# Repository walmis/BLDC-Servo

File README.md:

# BLDC-Servo

This project implements a FOC motor controller board for 57BLF0x series NEMA brushless motor.

The project goals are:
* to be inexpensive
* fully support FOC drive
* smooth operation for FFB devices
* Large stalled torque == relatively large current drive

The main components are:
* STM32L412 or STM32F103C8T6 MCU
* NCP81151 - MOSFET Gate drivers
* NCS213/INA213 current sense amplifiers
* FDMS8018 N-channel MOSFETS (can be any TDSON-8 30V>= MOSFETS with required current rating)
* MP2359 DC-DC step-down
* SN75176B RS485 transceiver

The board attaches directly to the motor casing with mosfets in direct contact (with thermal paste). This makes a good heatsink for power dissipation.

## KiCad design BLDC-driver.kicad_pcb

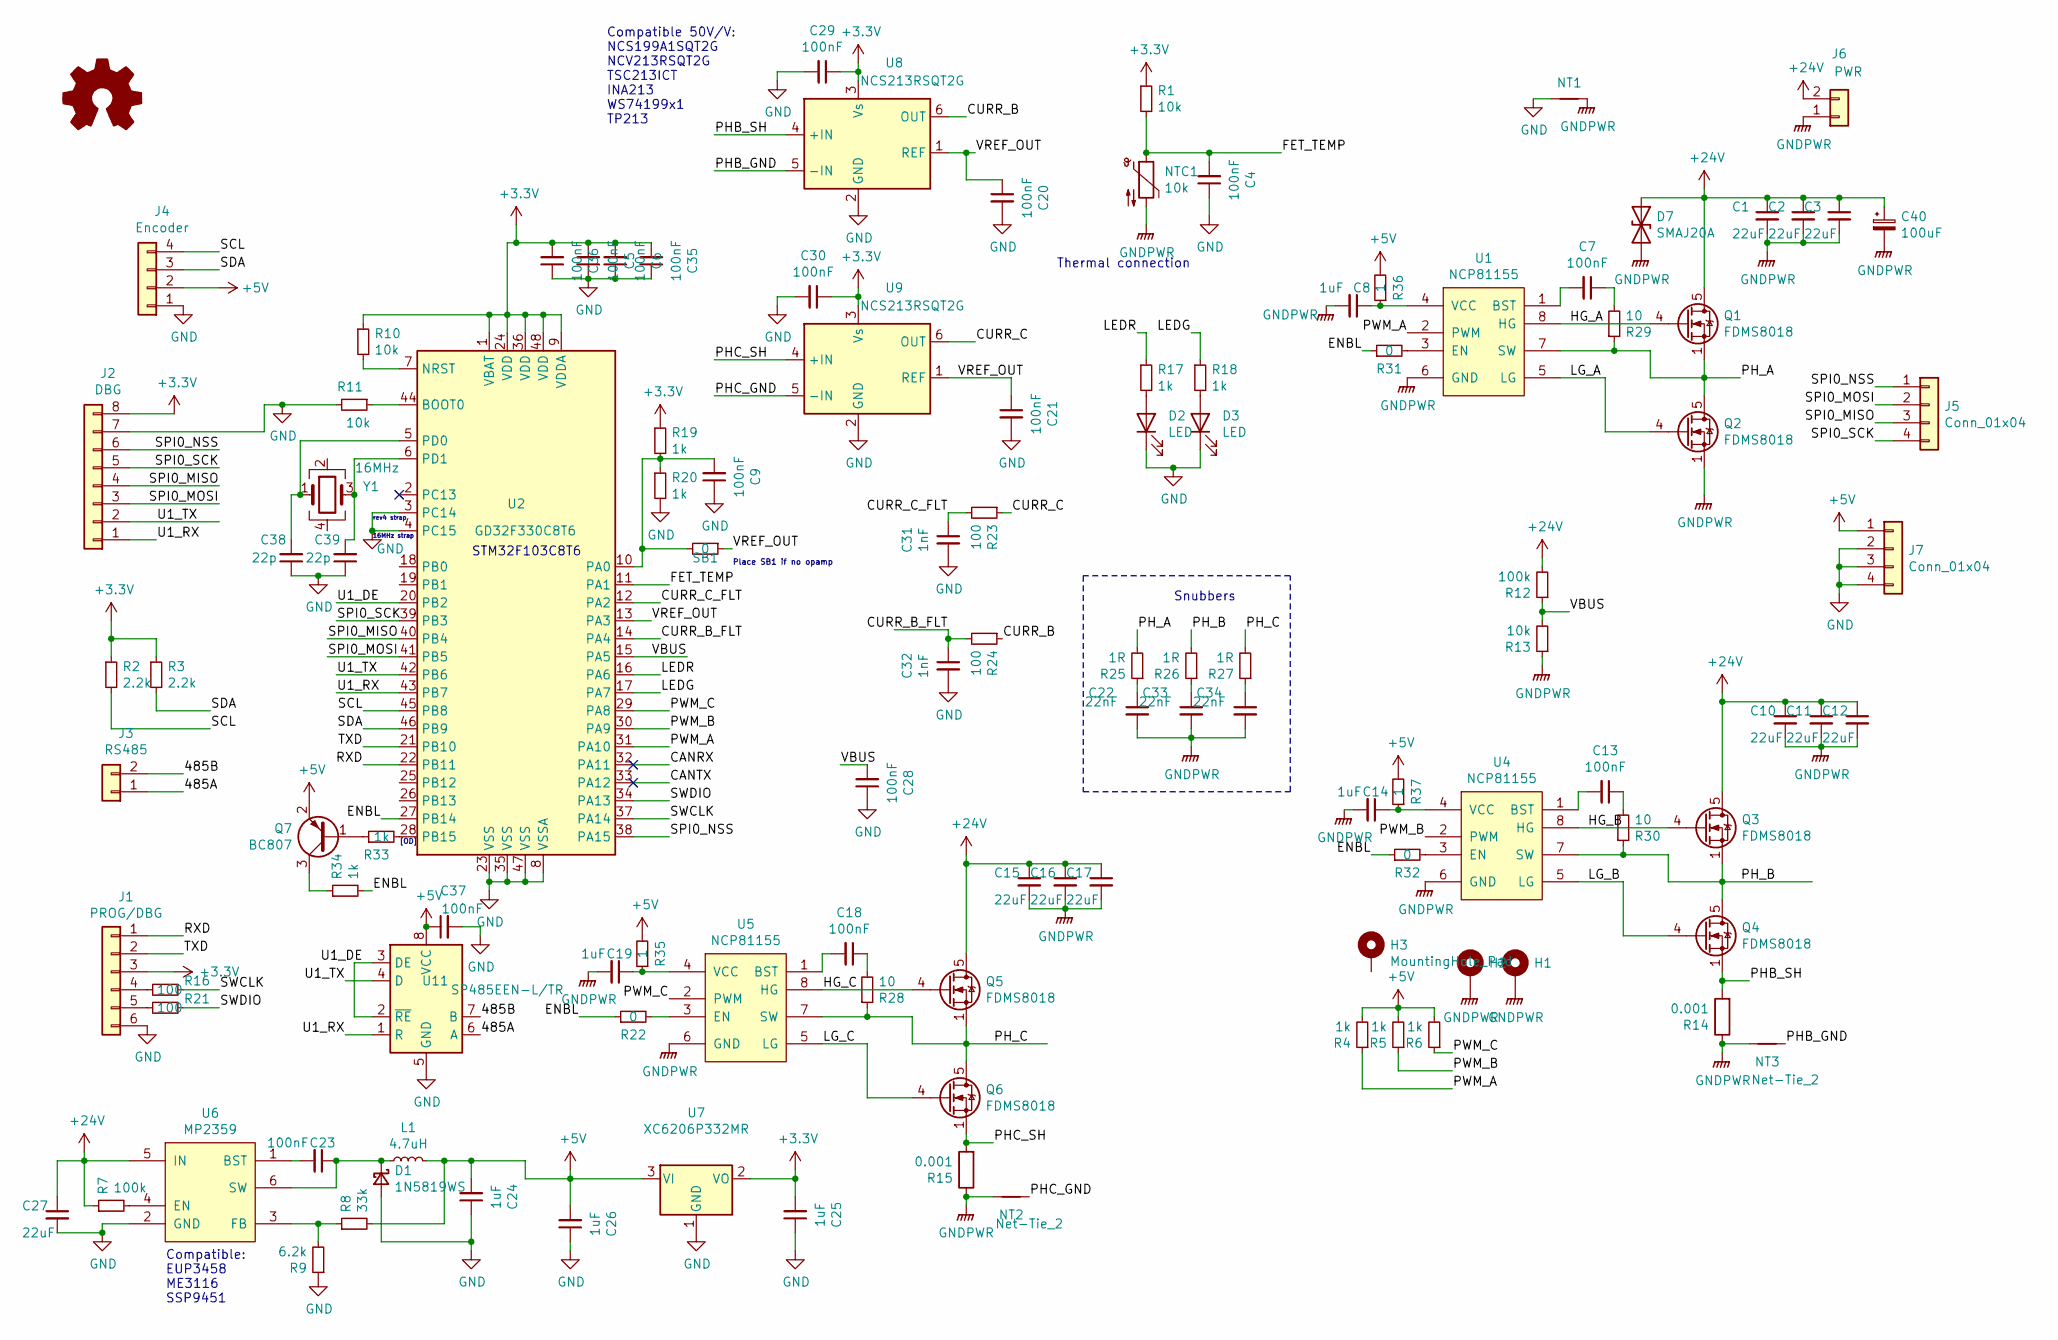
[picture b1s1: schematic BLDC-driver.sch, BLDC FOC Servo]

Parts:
C1, C2, C3, C10, C11, C12, C15, C16, C17, C27: 22uF; C_1206_3216Metric; MPN CL31A226KAHNNNE; JLCSMT C12891
C4, C5, C6, C7, C9, C13, C18, C20, C21, C23, C28, C29, C30, C35, C36, C37: 100nF; C_0402_1005Metric; MPN CL05B104KO5NNNC; JLCSMT C1525
C8, C14, C19, C24: 1uF; C_0402_1005Metric; MPN CL05A105KA5NQNC; JLCSMT C52923
C22, C33, C34: 22nF; C_0402_1005Metric; MPN 0402B223K500NT; JLCSMT C1532
C25, C26: 1uF; C_0603_1608Metric; MPN CL10A105KB8NNNC; JLCSMT C15849
C31, C32: 1nF; C_0402_1005Metric; MPN 0402B102K500NT; JLCSMT C1523
C38, C39: 22p; C_0402_1005Metric; MPN 0402CG220J500NT; JLCSMT C1555
C40: 100uF; CP_Elec_8x6.5; MPN UT1E101M0806VG; JLCSMT C393805
D1: 1N5819WS; D_SOD-323; MPN 1N5819WS; JLCSMT C191023
D2, D3: LED; LED_0603_1608Metric; MPN 19-217/GHC-YR1S2/3T; JLCSMT C72043
D7: SMAJ20A; D_SMB; MPN SMAJ20CA; JLCSMT C309871
H1, H2, H3: MountingHole_Pad; MountingHole_3.2mm_M3_DIN965_Pad_TopOnly; JLCPCB_IGNORE 1
J1: PROG/DBG; JST_PH_S6B-PH-K_1x06_P2.00mm_Horizontal; JLCPCB_IGNORE 1
J2: DBG; PinHeader_1x08_P2.00mm_Vertical; JLCPCB_IGNORE 1
J3: RS485; JST_PH_S2B-PH-K_1x02_P2.00mm_Horizontal; JLCPCB_IGNORE 1
J4: Encoder; PinSocket_1x04_P2.00mm_Vertical; JLCPCB_IGNORE 1
J5, J7: Conn_01x04; PinHeader_1x04_P2.00mm_Vertical; JLCPCB_IGNORE 1
J6: PWR; JST_VH_B2PS-VH_1x02_P3.96mm_Horizontal; JLCPCB_IGNORE 1
L1: 4.7uH; L_Taiyo-Yuden_MD-3030; MPN WPN3012HS4R7MT; JLCSMT C305275
NT1, NT2, NT3: Net-Tie_2; NetTie-2_SMD_Pad0.5mm; JLCPCB_IGNORE 1
NTC1: 10k; R_0603_1608Metric; MPN NCP18XH103F03RB; JLCSMT C13564
Q1, Q2, Q3, Q4, Q5, Q6: FDMS8018; JLCPCB_IGNORE 1
Q7: BC807; SOT-23; MPN MMBT5401; JLCSMT C8326
R1, R10, R11, R13: 10k; R_0402_1005Metric; MPN 0402WGF1002TCE; JLCSMT C25744
R2, R3: 2.2k; R_0603_1608Metric; MPN 0603WAF2201T5E; JLCSMT_PKG 0603
R4, R5, R6, R19, R20, R33, R34: 1k; R_0402_1005Metric; MPN 0402WGF1001TCE; JLCSMT_PKG 0402
R7, R12: 100k; R_0402_1005Metric; MPN 0402WGF1003TCE; JLCSMT C25741
R8: 33k; R_0603_1608Metric; MPN 0603WAF3302T5E; JLCSMT C4216
R9: 6.2k; R_0603_1608Metric; MPN 0603WAF6201T5E; JLCSMT_PKG 0603
R14, R15: 0.001; R_1210_3225Metric; MPN LR1206-21R001F4; JLCSMT C154629
R16, R21, R23, R24: 100; R_0402_1005Metric; MPN 0402WGF1000TCE; JLCSMT_PKG 0402
R17, R18: 1k; R_0603_1608Metric; MPN 0603WAF1001T5E; JLCSMT_PKG 0603
R22, R31, R32: 0; R_0603_1608Metric; MPN 0603WAF0000T5E; JLCSMT C21189
R25, R26, R27: 1R; R_0402_1005Metric; MPN 0402WGF100KTCE; JLCSMT_PKG 0402
R28, R29, R30: 10; R_0402_1005Metric; MPN 0402WGF100JTCE; JLCSMT_PKG 0402
R35, R36, R37: 1; R_0402_1005Metric; MPN 0402WGF100KTCE; JLCSMT C25086
SB1: 0; R_0402_1005Metric; MPN 0402WGF0000TCE; JLCSMT C17168
U1, U4, U5: NCP81155; DFN-8-1EP_3x3mm_P0.5mm_EP1.66x2.38mm; MPN NCP81155MNTXG; JLCSMT C173765
U2: GD32F330C8T6; LQFP-48_7x7mm_P0.5mm; MPN GD32F330C8T6; JLCSMT C129291
U6: MP2359; SOT-23-6; MPN MP2359DJ-LF-Z; JLCSMT C14259
U7: XC6206P332MR; SOT-23; MPN XC6206P332MR; JLCSMT C5446
U8, U9: NCS213RSQT2G; SOT-363_SC-70-6; MPN INA199A1DCKR; JLCSMT C59135
U11: SP485EEN-L/TR; SOIC-8_3.9x4.9mm_P1.27mm; MPN SP485EEN-L/TR; JLCSMT C6855
Y1: 16MHz; Crystal_SMD_3225-4Pin_3.2x2.5mm; MPN X322516MLB4SI; JLCSMT C13738

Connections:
+3V3: C5.2, C6.2, C25.2, C29.1, C30.1, C35.2, C36.2, J1.3, J2.8, R1.1, R2.1, R3.1, R10.1, R19.1, U2.1 (VBAT), U2.9 (VDDA), U2.24 (VDD), U2.36 (VDD), U2.48 (VDD), U7.2 (VO), U8.3 (Vs), U9.3 (Vs)
+5V: C24.2, C26.2, C37.1, J4.2, J7.1, L1.2, Q7.2 (E), R4.2, R5.2, R6.2, R8.2, R35.2, R36.2, R37.2, U7.3 (VI), U11.8 (VCC)
+24V: C1.1, C2.1, C3.1, C10.1, C11.1, C12.1, C15.1, C16.1, C17.1, C27.1, C40.1, D7.1 (A1), J6.2, Q1.5 (D), Q3.5 (D), Q5.5 (D), R7.1, R12.2, U6.5 (IN)
/485A: J3.1, U11.6 (A)
/485B: J3.2, U11.7 (B)
/CANRX: U2.32 (PA11)
/CANTX: U2.33 (PA12)
/CURR_B: R24.1, U8.6 (OUT)
/CURR_B_FLT: C32.1, R24.2, U2.14 (PA4)
/CURR_C: R23.1, U9.6 (OUT)
/CURR_C_FLT: C31.1, R23.2, U2.12 (PA2)
/ENBL: R22.1, R31.1, R32.1, R34.2, U2.27 (PB14)
/FET_TEMP: C4.2, NTC1.1, R1.2, U2.11 (PA1)
/HG_A: Q1.4 (G), U1.8 (HG)
/HG_B: Q3.4 (G), U4.8 (HG)
/HG_C: Q5.4 (G), U5.8 (HG)
/LEDG: R18.1, U2.17 (PA7)
/LEDR: R17.1, U2.16 (PA6)
/LG_A: Q2.4 (G), U1.5 (LG)
/LG_B: Q4.4 (G), U4.5 (LG)
/LG_C: Q6.4 (G), U5.5 (LG)
/PHB_GND: NT3.2, U8.5 (-IN)
/PHB_SH: Q4.1 (S), Q4.2 (S), Q4.3 (S), R14.2, U8.4 (+IN)
/PHC_GND: NT2.2, U9.5 (-IN)
/PHC_SH: Q6.1 (S), Q6.2 (S), Q6.3 (S), R15.2, U9.4 (+IN)
/PH_A: Q1.1 (S), Q1.2 (S), Q1.3 (S), Q2.5 (D), R25.2, R29.1, U1.7 (SW)
/PH_B: Q3.1 (S), Q3.2 (S), Q3.3 (S), Q4.5 (D), R26.2, R30.1, U4.7 (SW)
/PH_C: Q5.1 (S), Q5.2 (S), Q5.3 (S), Q6.5 (D), R27.2, R28.1, U5.7 (SW)
/PWM_A: R4.1, U1.2 (PWM), U2.31 (PA10)
/PWM_B: R5.1, U2.30 (PA9), U4.2 (PWM)
/PWM_C: R6.1, U2.29 (PA8), U5.2 (PWM)
/RXD: J1.1, U2.22 (PB11)
/SCL: J4.4, R2.2, U2.45 (PB8)
/SDA: J4.3, R3.2, U2.46 (PB9)
/SPI0_MISO: J2.4, J5.3, U2.40 (PB4)
/SPI0_MOSI: J2.3, J5.2, U2.41 (PB5)
/SPI0_NSS: J2.6, J5.1, U2.38 (PA15)
/SPI0_SCK: J2.5, J5.4, U2.39 (PB3)
/SWCLK: R16.1, U2.37 (PA14)
/SWDIO: R21.1, U2.34 (PA13)
/TXD: J1.2, U2.21 (PB10)
/U1_DE: U2.20 (PB2), U11.2 (~RE), U11.3 (DE)
/U1_RX: J2.1, U2.43 (PB7), U11.1 (R)
/U1_TX: J2.2, U2.42 (PB6), U11.4 (D)
/VBUS: C28.2, R12.1, R13.2, U2.15 (PA5)
/VREF_OUT: C20.1, C21.1, SB1.1, U2.13 (PA3), U8.1 (REF), U9.1 (REF)
GND: C4.1, C5.1, C6.1, C9.1, C20.2, C21.2, C24.1, C25.1, C26.1, C27.2, C28.1, C29.2, C30.2, C31.2, C32.2, C35.1, C36.1, C37.2, C38.1, C39.1, D1.2 (A), D2.1 (K), D3.1 (K), J1.6, J2.7, J4.1, J7.2, J7.3, J7.4, NT1.1, R9.1, R11.2, R20.2, U2.3 (PC14), U2.4 (PC15), U2.8 (VSSA), U2.23 (VSS), U2.35 (VSS), U2.47 (VSS), U6.2 (GND), U7.1 (GND), U8.2 (GND), U9.2 (GND), U11.5 (GND)
GNDPWR: C1.2, C2.2, C3.2, C8.2, C10.2, C11.2, C12.2, C14.2, C15.2, C16.2, C17.2, C19.2, C22.2, C33.2, C34.2, C40.2, D7.2 (A2), H1.1, H2.1, J6.1, NT1.2, NT2.1, NT3.1, NTC1.2, Q2.1 (S), Q2.2 (S), Q2.3 (S), R13.1, R14.1, R15.1, U1.6 (GND), U1.9 (PAD), U4.6 (GND), U4.9 (PAD), U5.6 (GND), U5.9 (PAD)
unnamed: C7.1, R29.2
unnamed: C7.2, U1.1 (BST)
unnamed: C8.1, R36.1, U1.4 (VCC)
unnamed: C9.2, R19.2, R20.1, SB1.2, U2.10 (PA0)
unnamed: C13.1, R30.2
unnamed: C13.2, U4.1 (BST)
unnamed: C14.1, R37.1, U4.4 (VCC)
unnamed: C18.1, R28.2
unnamed: C18.2, U5.1 (BST)
unnamed: C19.1, R35.1, U5.4 (VCC)
unnamed: C22.1, R25.1
unnamed: C23.1, D1.1 (K), L1.1, U6.6 (SW)
unnamed: C23.2, U6.1 (BST)
unnamed: C33.1, R26.1
unnamed: C34.1, R27.1
unnamed: C38.2, U2.5 (PD0), Y1.1
unnamed: C39.2, U2.6 (PD1), Y1.3
unnamed: D2.2 (A), R17.2
unnamed: D3.2 (A), R18.2
unnamed: J1.4, R16.2
unnamed: J1.5, R21.2
unnamed: Q7.1 (B), R33.1
unnamed: Q7.3 (C), R34.1
unnamed: R7.2, U6.4 (EN)
unnamed: R8.1, R9.2, U6.3 (FB)
unnamed: R10.2, U2.7 (NRST)
unnamed: R11.1, U2.44 (BOOT0)
unnamed: R22.2, U5.3 (EN)
unnamed: R31.2, U1.3 (EN)
unnamed: R32.2, U4.3 (EN)
unnamed: R33.2, U2.28 (PB15)

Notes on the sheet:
Thermal connection
Snubbers
Place SB1 if no opamp
[OD]
Compatible 50V/V: NCS199A1SQT2G NCV213RSQT2G TSC213ICT INA213 WS74199x1 TP213
STM32F103C8T6
16MHz strap
Compatible: EUP3458 ME3116 SSP9451
rev4 strap

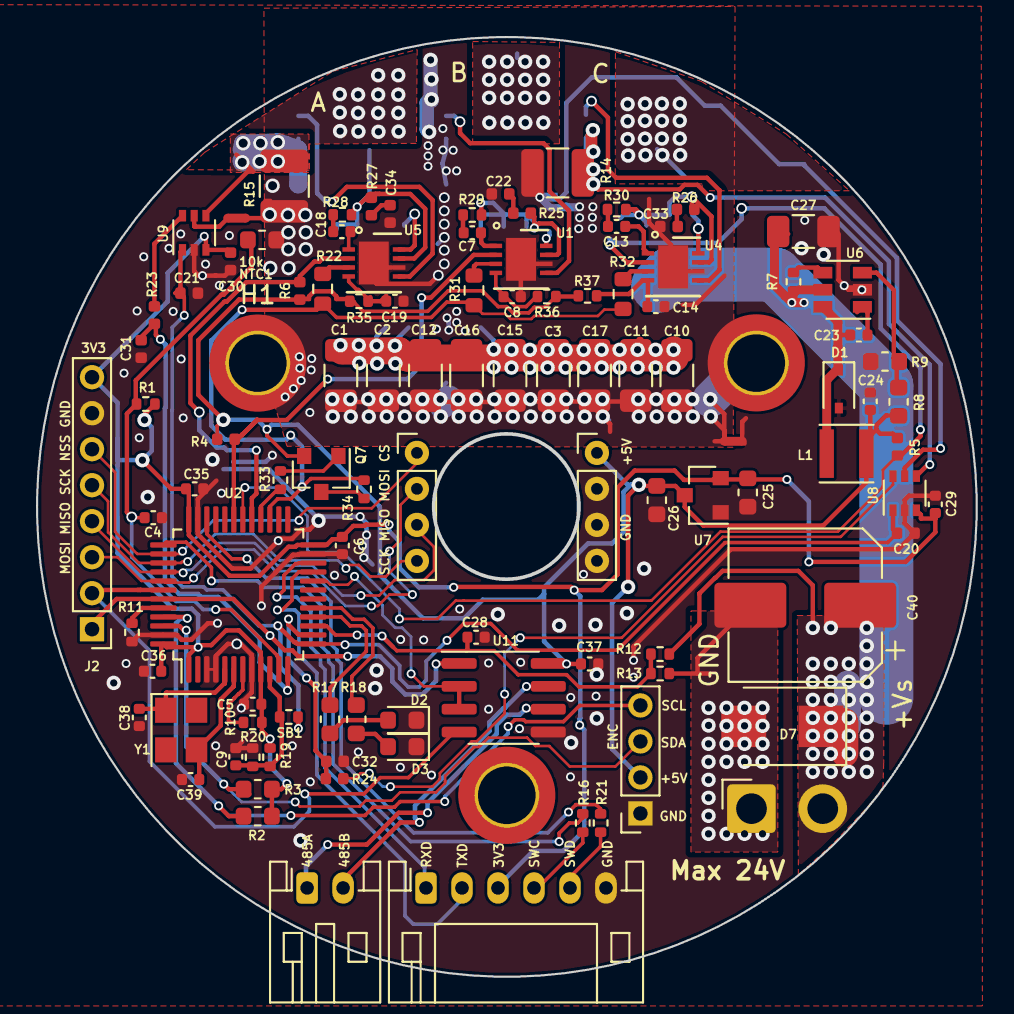
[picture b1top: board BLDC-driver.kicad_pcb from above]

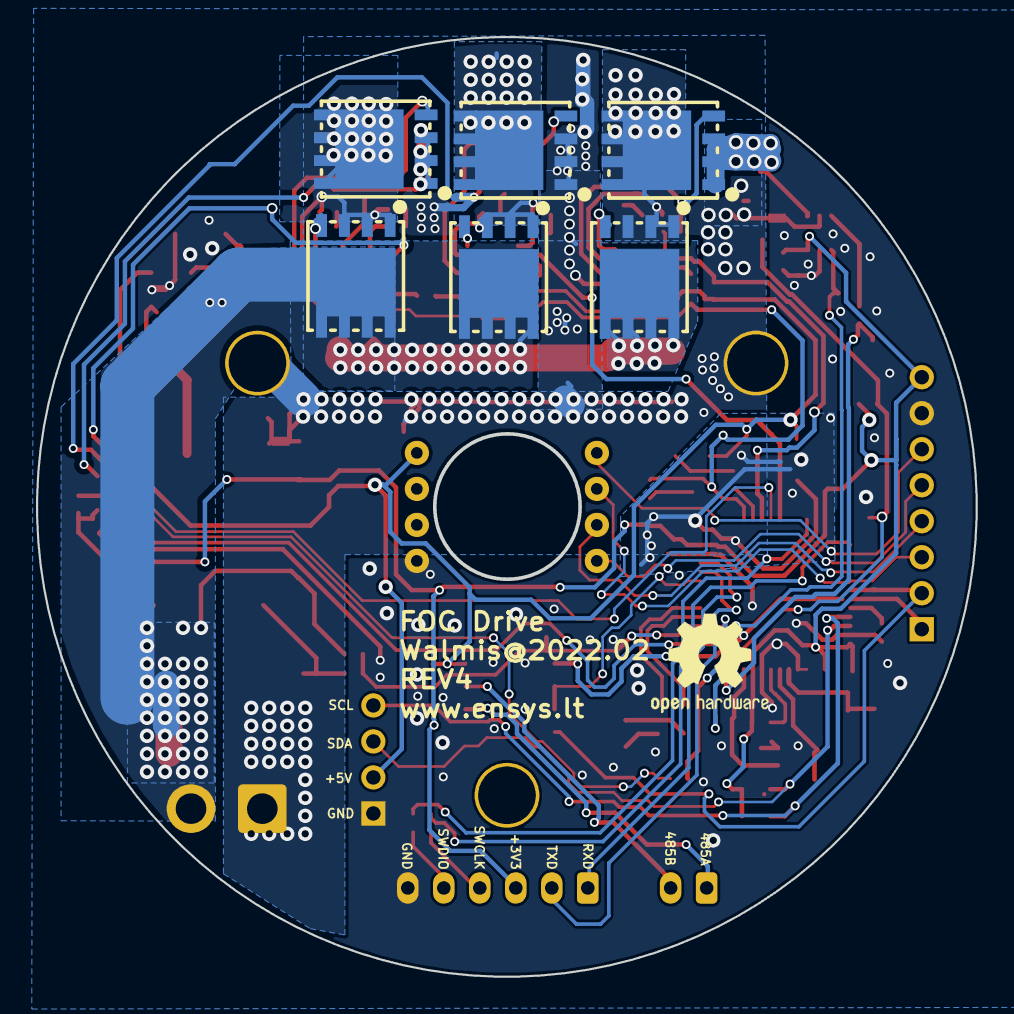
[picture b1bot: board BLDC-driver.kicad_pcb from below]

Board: 2 copper layers, 52.1 x 52.1 mm, 114 parts (7 on the bottom side), 77 nets.

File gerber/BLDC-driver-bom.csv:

"comment","designator","footprint","LCSC Part"
"100nF","C4,C5,C6,C7,C9,C13,C18,C20,C21,C23,C28,C29,C30,C35,C36,C37","0402","C1525"
"10uF","C1,C2,C3,C10,C11,C12,C15,C16,C17,C27","1206","C13585"
"1uF","C8,C14,C19,C24","0402","C52923"
"10k","NTC1","RES-SMD","C13564"
"10k","R1,R10,R11,R13","0402","C25744"
"1uF","C25,C26","0603","C15849"
"MP2359","U6","TSOT-23-6","C14259"
"6.2k","R9","0603","C4260"
"33k","R8","0603","C4216"
"4.7uH","L1","SMD,3x3x1.2mm","C305275"
"100k","R7,R12","0402","C25741"
"1k","R17,R18","0603","C21190"
"LED","D3","LED_0603","C72043"
"LED","D2","0603","C2286"
"0.001","R14,R15","RES-SMD","C154629"
"SMAJ24A","D7","SMA,DO-214AC","C10769"
"100","R16,R21,R23,R24","0402","C25076"
"1nF","C31,C32","0402","C1523"
"2.2k","R2,R3","0603","C4190"
"1k","R4,R5,R6,R19,R20,R33,R34","0402","C11702"
"1R","R25,R26,R27,R35,R36,R37","0402","C25086"
"22nF","C22,C33,C34","0402","C1532"
"10","R28,R29,R30","0402","C25077"
"SN75176AD","U11","SOIC-8_3.9x4.9x1.27P","C7063"
"0","SB1","0402","C17168"
"0","R22,R31,R32","0603","C21189"
"BC807","Q7","SOT-23-3","C8326"
"16MHz","Y1","SMD-CRY-3225_4P","C13738"
"22p","C38,C39","0402","C1555"

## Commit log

2020-06-15 init
2020-06-15 annotate
2020-06-15 Schematic progress
2020-06-16 Latest
2020-06-18 Change to stm32f103c8t6
2020-06-29 Change i2c resistor to 2.2k
2020-07-05 add pwm 5v pull up
2020-07-07 Add snubbers
2020-07-09 add usart dev
2021-01-15 Revision 2 update
    Move current shunts to low side. I have encountered smoke from current
    amplifiers when working @ 20V.
    Adapt to STM32L4xxCBT mcu.
    Add snubbers and resistance to gate drivers to reduce ringing due to
    very fast switching.
    Add RS485 interface instead of CAN
2021-01-15 Add pictures, remove test dir
2021-01-15 Add schematic pdf
2021-01-15 Crop images
2021-01-15 Add MPNs for some parts
2021-07-09 Multiple updates:
    Change amp filter caps to 1nF
    Move second shunt resistor to top layer
    Make one hole grounded
    various routing updates
2021-07-09 Rev3: Update connectors, add JST PH connectors
2021-07-09 Update images, readme
2021-08-18 Update BOM, change crystal to 16Mhz
2021-08-18 Add JLCPCB order files
2021-10-01 Add encoder FFC connector, change NCP drivers to JLC sourceable
2021-10-01 Update JLC BOM
2021-10-01 Update 3V3 LDO
2021-10-03 Add DC-DC compatible notes
2021-10-03 Add another alt
2022-01-31 Rev 4 update
2022-02-01 Latest revision
2022-02-02 Rev 4
